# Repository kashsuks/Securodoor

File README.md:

# Securodoor

Securodoor is a wireless smart doorbell system that uses a esp32-cam in order to monitor your porch!!

## Why did i build this

Welp I just moved into a new house and as expected, there isnt any smart doorbell or anything, so I decided to make my own, at my own ease. I wanted it to be able to send messages to my phone when I have someone at the door and the microphone is so I can hear the other person on the end

## Any cool ideas I had in this project

Since the esp32 cam doesnt have its own microphone module, I decided to use a microphone amplifier and merge the Audio from the mic and the Video from the camera in order to have A/V for my footage

## My images!!

Schematic:

PCB:

3D Model of PCB:

3d Model of my Case!!:

I realized that I didn't need a PCB since I wont be using it and instead handwiring everything a bit too late :D

## BOM
| Product Name           | Price   | Link                                                                                                                                                                                                                                                                                                                                                                                                                                                                                                                                                                                                                                      | Quantity |
|------------------------|---------|-------------------------------------------------------------------------------------------------------------------------------------------------------------------------------------------------------------------------------------------------------------------------------------------------------------------------------------------------------------------------------------------------------------------------------------------------------------------------------------------------------------------------------------------------------------------------------------------------------------------------------------------|----------|
| Esp32-cam              | $6.15   | [Link](https://www.aliexpress.com/item/1005003472117545.html?spm=a2g0o.productlist.main.1.1a70LFBALFBA1p&algo_pvid=72696f4e-266f-48a9-9997-3a669fbe0acf&algo_exp_id=72696f4e-266f-48a9-9997-3a669fbe0acf-0&pdp_ext_f=%7B%22order%22%3A%222384%22%2C%22eval%22%3A%221%22%7D&pdp_npi=4%40dis%21CAD%212.40%211.70%21%21%211.71%211.21%21%40210313e917489206007412128e3eda%2112000025941403906%21sea%21CA%210%21ABX&curPageLogUid=gFy8A0obYYaC&utparam-url=scene%3Asearch%7Cquery_from%3A) | 1        |
| Open Push Button       | $0.90   | [Link](https://www.aliexpress.com/item/4000330112297.html?src=bing&aff_short_key=UneMJZVf&aff_platform=true&isdl=y)                                                                                                                                                                                                                                                                                                                                                                                                                                                                                                                    | 1        |
| Red LED (I have this)  | $5.95   | [Link](https://www.amazon.com/Novelty-Place-Colors-Yellow-Lights/dp/B086V2M2TT?th=1)                                                                                                                                                                                                                                                                                                                                                                                                                                                                                                                                                       | 1        |
| Blue LED (I have this) | $5.95   | [Link](https://www.amazon.com/Novelty-Place-Colors-Yellow-Lights/dp/B086V2M2TT?th=1)                                                                                                                                                                                                                                                                                                                                                                                                                                                                                                                                                       | 1        |
| USB-C Breakout Board   | $2.62   | [Link](https://www.aliexpress.com/item/1005007382623157.html?spm=a2g0o.productlist.main.32.5d5cHfcBHfcBey)                                                                                                                                                                                                                                                                                                                                                                                                                                                                                                                              | 1        |
| Max9814 Amplifier      | $1.86   | [Link](https://www.aliexpress.com/item/1005006072505538.html?spm=a2g0o.productlist.main.6.2b142437j6bhTN)                                                                                                                                                                                                                                                                                                                                                                                                                                                                                                                                 | 1        |
| 5V Passive Buzzer      | $7.28   | [Link](https://www.amazon.com/Gikfun-Terminals-Passive-Electronic-Arduino/dp/B01GJLE5BS)                                                                                                                                                                                                                                                                                                                                                                                                                                                                                                                                                   | 1        |
| 1k Ohm Resistor        | $0.10   | [Link](https://www.digikey.ca/en/products/detail/yageo/CFR-25JT-52-1K/13921014)                                                                                                                                                                                                                                                                                                                                                                                                                                                                                                                                                           | 2        |
| 10k Ohm Resistor       | $3.99   | [Link](https://us.amazon.com/California-JOS-Carbon-Resistor-Tolerance/dp/B0BR68QQPF?sr=8-3)                                                                                                                                                                                                                                                                                                                                                                                                                                                                                                                                                 | 2        |
| 5.1k Ohm Resistor      | $6.05   | [Link](https://www.amazon.com/Projects-5-1k-Resistors-Choose-Quantity/dp/B0185FD0WG)                                                                                                                                                                                                                                                                                                                                                                                                                                                                                                                                                       | 2        |

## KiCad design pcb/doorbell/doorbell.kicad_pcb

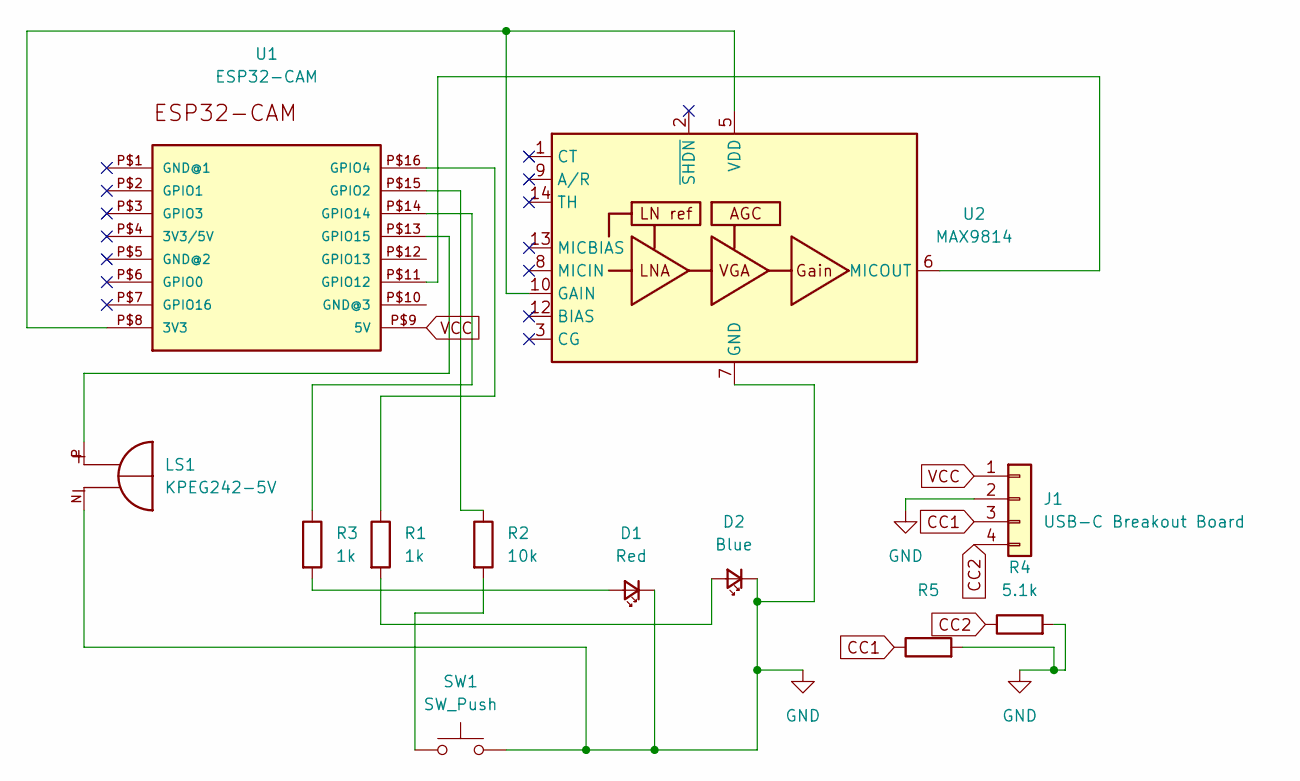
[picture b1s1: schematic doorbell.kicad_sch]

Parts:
D1: Red; LED_D5.0mm
D2: Blue; LED_D5.0mm
J1: USB-C Breakout Board; FanPinHeader_1x04_P2.54mm_Vertical
LS1: KPEG242-5V; XDCR_KPEG242-5V; PARTREV 1.1
R1, R3: 1k; R_Axial_DIN0207_L6.3mm_D2.5mm_P7.62mm_Horizontal
R2: 10k; R_Axial_DIN0207_L6.3mm_D2.5mm_P7.62mm_Horizontal
R4, R5: 5.1k; R_Axial_DIN0207_L6.3mm_D2.5mm_P7.62mm_Horizontal
SW1: SW_Push; SW_PUSH_6mm_H13mm
U1: ESP32-CAM
U2: MAX9814; SON40P300X300X80-15N

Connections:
CC1: J1.3, R5.1
CC2: J1.4, R4.1
GND: D1.1 (K), D2.1 (K), J1.2, LS1.N, R4.2, R5.2, SW1.2, U2.4 (GND), U2.7 (GND), U2.11 (GND), U2.15 (GND)
unnamed: D1.2 (A), R3.2
unnamed: D2.2 (A), R1.2
unnamed: R2.2, SW1.1
unnamed: U1.P$8 (3V3), U2.5 (VDD), U2.10 (GAIN)
unnamed: R2.1, U1.P$15 (GPIO2)
unnamed: R1.1, U1.P$16 (GPIO4)
unnamed: U1.P$11 (GPIO12), U2.6 (MICOUT)
unnamed: R3.1, U1.P$14 (GPIO14)
unnamed: LS1.P, U1.P$13 (GPIO15)
VCC: J1.1, U1.P$9 (5V)

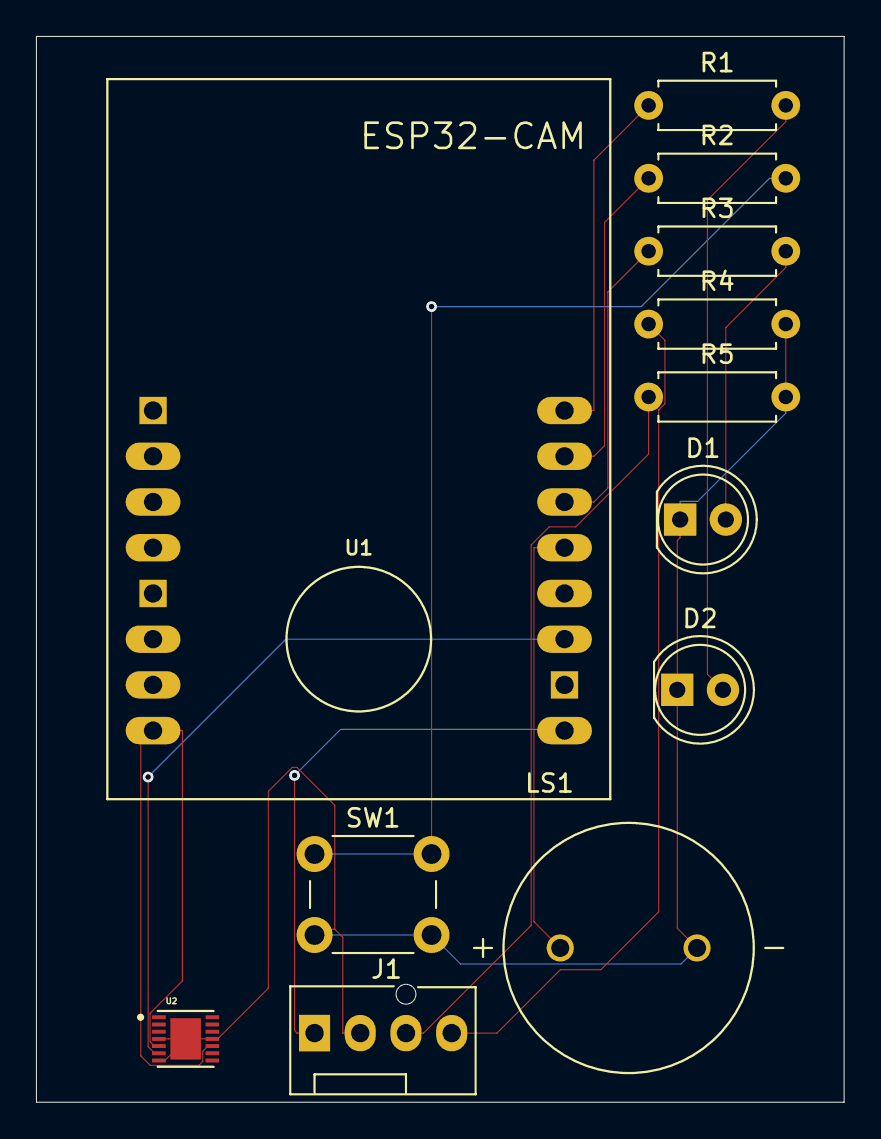
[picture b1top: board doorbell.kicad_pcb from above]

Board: 2 copper layers, 44.9 x 59.2 mm, 12 parts (0 on the bottom side), 13 nets.

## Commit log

2025-05-24 Rename README.md to journal.md
2025-05-24 Rename journal.md to JOURNAL.md
2025-06-02 folders
2025-06-02 removed the ds store
2025-06-03 CAD file!!!
2025-06-03 firmware!! i hope this works
2025-06-03 added bom
2025-06-03 updated file formatting
2025-06-06 Create something
2025-06-07 added my silkscreen art!!
